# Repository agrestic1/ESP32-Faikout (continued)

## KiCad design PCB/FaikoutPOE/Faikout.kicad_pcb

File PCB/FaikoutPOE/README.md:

# FaikoutPOE

## Trademark

This project is subject to the licence in the LICENCE file, and even if that says it is an open source project, you cannot sell boards or cases bearing the Andrews & Arnold Ltd name, the A&A logo, the registered trademark AJK logo, or other registered trademarks, or any GS1 allocated EANs/barcode assigned to Andrews & Arnold Ltd.

## PCB Designs

These files are for use with [KiCAD](https://www.kicad.org).

- [Faikout](Faikout.kicad_pro)

## 3D

3D case designs are normally automatically created from the PCB so as to ensure correct details and placement of apertures, etc.

|Design|Bottom|Top|Combined|
|------|------|---|--------|
|Faikout||||

## PCB Images Faikout

---

*Auto generated README.md 2026-10-20T12:44:44*

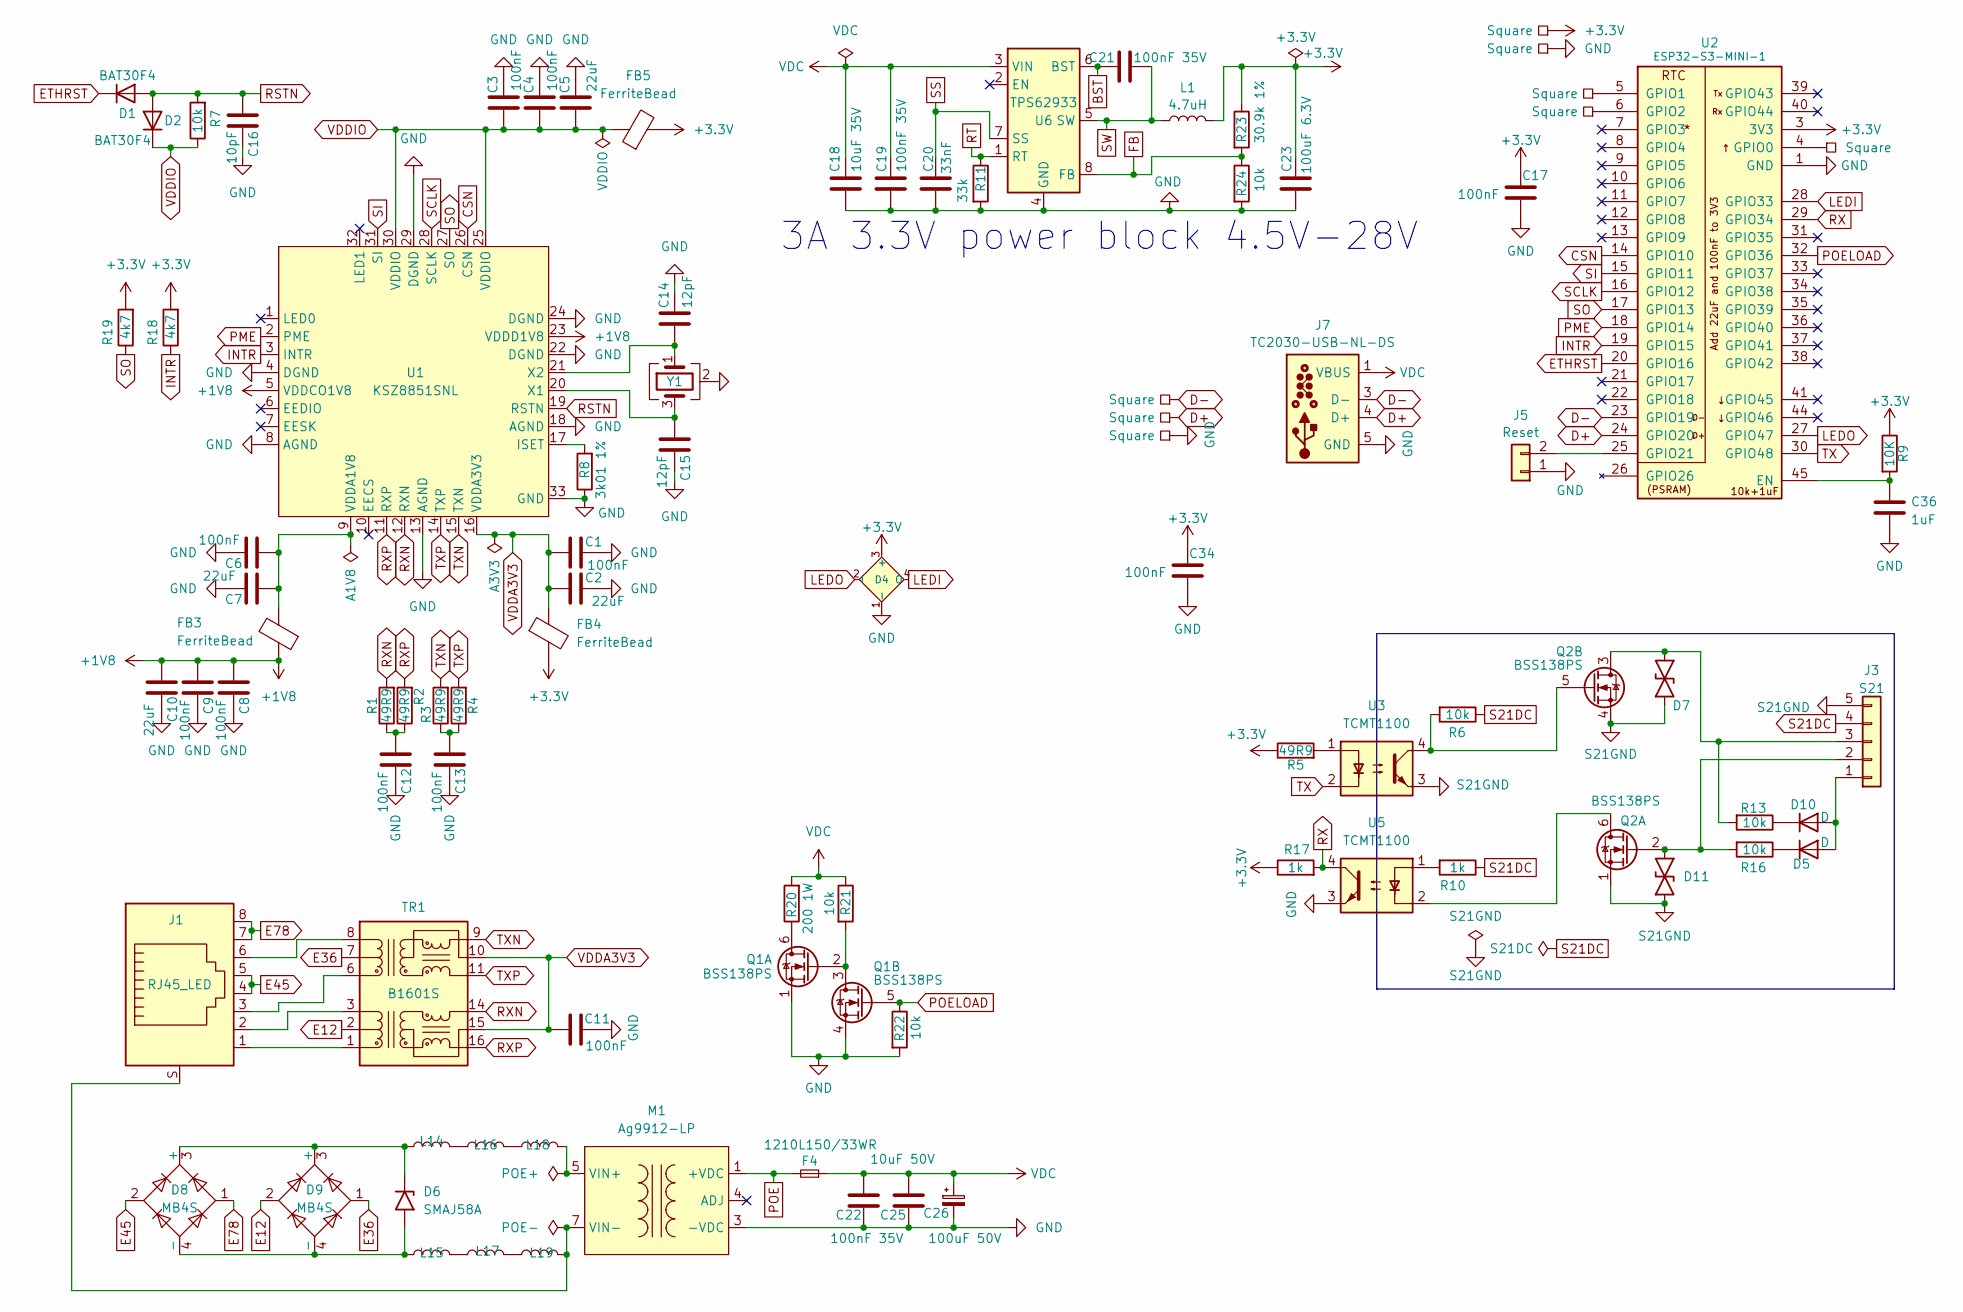
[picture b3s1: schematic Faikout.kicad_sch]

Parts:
C1, C3, C4, C6, C8, C9, C11, C12, C13: 100nF; C_0201; MPN C66938
C2, C5, C7, C10: 22uF; C_0402; MPN C105226
C14, C15: 12pF; C_0201
C16: 10pF; C_0201; MPN C76921
C17, C34: 100nF; C_0201; MPN C76934
C18: 10uF 35V; C_0603; MPN C22367827
C19, C21, C22: 100nF 35V; C_0201; MPN C181043
C20: 33nF; C_0201; MPN C5142554
C23: 100uF 6.3V; C_0805; MPN C141660
C25: 10uF 50V; C_1206; MPN C13585
C26: 100uF 50V; CP_Elec_6.3x7.7; MPN C72478
C36: 1uF; C_0201
D1, D2: BAT30F4; D_0201; MPN C18197832
D4: XL-1615RGBC-2812B; SMD1615-Side; MPN C5349954
D5, D10: D; D_0402; MPN C28642302
D6: SMAJ58A; D_SMA
D7, D11: DFN1006-2L; MPN C5137770
D8, D9: MB4S; TO-269AA-BR; MPN C232847
F4: 1210L150/33WR; Fuse_1210; MPN C42376299
FB3, FB4, FB5: FerriteBead; L_0603; MPN C14709
J1: RJ45_LED; RC01516; MPN C708636
J3: S21; JST_EH_S5B-EH_1x05_P2.50mm_Horizontal; MPN C265103
J5: Reset; AA-Pad
J7: TC2030-USB-NL-DS; Tag-Connect_TC2030-IDC-NL_2x03_P1.27mm_Vertical
L1: 4.7uH; L_6x6; MPN C32684
L14, L15, L16, L17, L18, L19: CBG201209U121T; L_0805; MPN C41330
M1: Ag9912-LP; Ag9900-LP; MPN C6789853
P1, P2, P3, P4, P5, P6, P7, P8: Square; PAD-2mm
Q1, Q2: BSS138PS; SOT-363_SC-70-6; MPN C193381
R1, R2, R3, R4, R5: 49R9; R_0201; MPN C100141
R6, R7, R13, R16, R21, R22, R24: 10k; R_0201; MPN C106225
R8: 3k01 1%; R_0201; MPN C320817
R9: 10K; R_0201; MPN C106225
R10, R17: 1k; R_0201; MPN C270365
R11: 33k; R_0201; MPN C473534
R18, R19: 4k7; R_0201; MPN C138135
R20: 200 1W; R_2512; MPN C2907575
R23: 30.9k 1%; R_0201; MPN C473585
TR1: B1601S; MPN C510548
U1: KSZ8851SNL; QFN-32-1EP_5x5mm_P0.5mm_EP3.7x3.7mm-hot; MPN C633272
U2: ESP32-S3-MINI-1; MPN C3013941
U3: TCMT1100; SOP-4_4.4x2.6mm_P1.27mm; MPN C118298
U5: TCMT1100; SOP-4_4.4x2.6mm_P1.27mm; MPN MPN
U6: TPS62933; SOT-583-8; MPN C3200405
Y1: Crystal_GND24; Crystal-3.2x2.5; MPN C5155480

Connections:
+1V8: C8.1, C9.1, C10.1, FB3.1, U1.5 (VDDCO1V8), U1.23 (VDDD1V8)
+3.3V: C17.2, C23.1, C34.2, D4.3 (+), FB4.2, FB5.2, L1.2, P7.1 (P_1), R5.1, R9.1, R17.1, R18.2, R19.2, R23.1, U2.3 (3V3)
BST: C21.1, U6.6 (BST)
CSN: U1.26 (CSN), U2.14 (GPIO10)
D+: J7.4 (D+), P3.1 (P_1), U2.24 (GPIO20)
D-: J7.2 (NC), J7.3 (D-), J7.6 (NC), P2.1 (P_1), U2.23 (GPIO19)
E12: D9.2, TR1.2 (C_TD)
E36: D9.1, TR1.7 (C_RD)
E45: D8.2, J1.4, J1.5
E78: D8.1, J1.7, J1.8
ETHRST: D1.1 (K), U2.20 (GPIO16)
FB: R23.2, R24.1, U6.8 (FB)
GND: C1.2, C2.2, C3.2, C4.2, C5.2, C6.2, C7.2, C8.2, C9.2, C10.2, C11.2, C12.2, C13.2, C14.2, C15.2, C16.2, C17.1, C18.2, C19.2, C20.2, C22.2, C23.2, C25.1, C26.2, C34.1, C36.2, D4.1 (-), J5.1, J7.5 (GND), M1.3 (-VDC), P4.1 (P_1), P8.1 (P_1), Q1.1 (SN), Q1.4 (DP), R8.1, R11.2, R22.2, R24.2, U1.4 (DGND), U1.8 (AGND), U1.13 (AGND), U1.18 (AGND), U1.22 (DGND), U1.24 (DGND), U1.29 (DGND), U1.33 (GND), U2.1 (GND), U2.2 (GND), U2.42 (GND), U2.43 (GND), U2.46 (GND), U2.47 (GND), U2.48 (GND), U2.49 (GND), U2.50 (GND), U2.51 (GND), U2.52 (GND), U2.53 (GND), U2.54 (GND), U2.55 (GND), U2.56 (GND), U2.57 (GND), U2.58 (GND), U2.59 (GND), U2.60 (GND), U2.61 (GND), U2.62 (GND), U2.63 (GND), U2.64 (GND), U2.65 (GND), U5.3, U6.4 (GND), Y1.2 (G), Y1.4 (G)
INTR: R18.1, U1.3 (INTR), U2.19 (GPIO15)
LEDI: D4.4 (O), U2.28 (GPIO33)
LEDO: D4.2 (I), U2.27 (GPIO47)
unnamed: C12.1, R1.1, R2.1
unnamed: C13.1, R3.1, R4.1
unnamed: D5.1 (K), R16.1
unnamed: D6.1 (A1), D8.3 (+), D9.3 (+), L14.1
unnamed: D6.2 (A2), D8.4 (-), D9.4 (-), L15.1
unnamed: D5.2 (A), D10.2 (A), J3.1
unnamed: D10.1 (K), R13.1
unnamed: D11.1, J3.2, Q2.2 (GN), R16.2
unnamed: D7.2, J3.3, Q2.3 (SP), R13.2
unnamed: J5.2, U2.25 (GPIO21)
unnamed: L14.2, L16.1
unnamed: L15.2, L17.1
unnamed: L16.2, L18.1
unnamed: L17.2, L19.1
unnamed: P1.1 (P_1), U2.4 (GPIO0)
unnamed: P5.1 (P_1), U2.5 (GPIO1)
unnamed: P6.1 (P_1), U2.6 (GPIO2)
unnamed: Q1.6 (DN), R20.1
unnamed: Q1.2 (GN), Q1.3 (SP), R21.2
unnamed: Q2.6 (DN), U5.2
unnamed: Q2.5 (GP), R6.2, U3.4
unnamed: R5.2, U3.1
unnamed: R10.2, U5.1
unnamed: J1.3, TR1.6 (RD+)
unnamed: J1.6, TR1.8 (RD-)
unnamed: J1.1, TR1.1 (TD+)
unnamed: J1.2, TR1.3 (TD-)
unnamed: R8.2, U1.17 (ISET)
unnamed: C6.1, C7.1, FB3.2, U1.9 (VDDA1V8)
unnamed: C15.1, U1.20 (X1), Y1.3
unnamed: C14.1, U1.21 (X2), Y1.1
unnamed: C36.1, R9.2, U2.45 (EN)
PME: U1.2 (PME), U2.18 (GPIO14)
POE: F4.2, M1.1 (+VDC), M1.2 (+VDC)
POELOAD: Q1.5 (GP), R22.1, U2.32 (GPIO36)
RSTN: C16.1, D1.2 (A), D2.2 (A), R7.2, U1.19 (RSTN)
RT: R11.1, U6.1 (RT)
RX: R17.2, U2.29 (GPIO34), U5.4
RXN: R1.2, TR1.14 (TX-), U1.12 (RXN)
RXP: R2.2, TR1.16 (TX+), U1.11 (RXP)
S21DC: J3.4, R6.1, R10.1
S21GND: D7.1, D11.2, J3.5, Q2.1 (SN), Q2.4 (DP), U3.3
SCLK: U1.28 (SCLK), U2.16 (GPIO12)
SI: U1.31 (SI), U2.15 (GPIO11)
SO: R19.1, U1.27 (SO), U2.17 (GPIO13)
SS: C20.1, U6.7 (SS)
SW: C21.2, L1.1, U6.5 (SW)
TX: U2.30 (GPIO48), U3.2
TXN: R3.2, TR1.9 (RX-), U1.15 (TXN)
TXP: R4.2, TR1.11 (RX+), U1.14 (TXP)
VDC: C18.1, C19.1, C22.1, C25.2, C26.1, F4.1, J7.1 (VBUS), R20.2, R21.1, U6.3 (VIN)
VDDA3V3: C1.1, C2.1, C11.1, FB4.1, TR1.10 (C_RX), TR1.15 (C_TX), U1.16 (VDDA3V3)
VDDIO: C3.1, C4.1, C5.1, D2.1 (K), FB5.1, R7.1, U1.25 (VDDIO), U1.30 (VDDIO)
VIN+: L18.2, M1.5 (VIN+), M1.6 (VIN+)
VIN-: J1.S, L19.2, M1.7 (VIN-), M1.8 (VIN-)

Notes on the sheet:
3A 3.3V power block 4.5V-28V

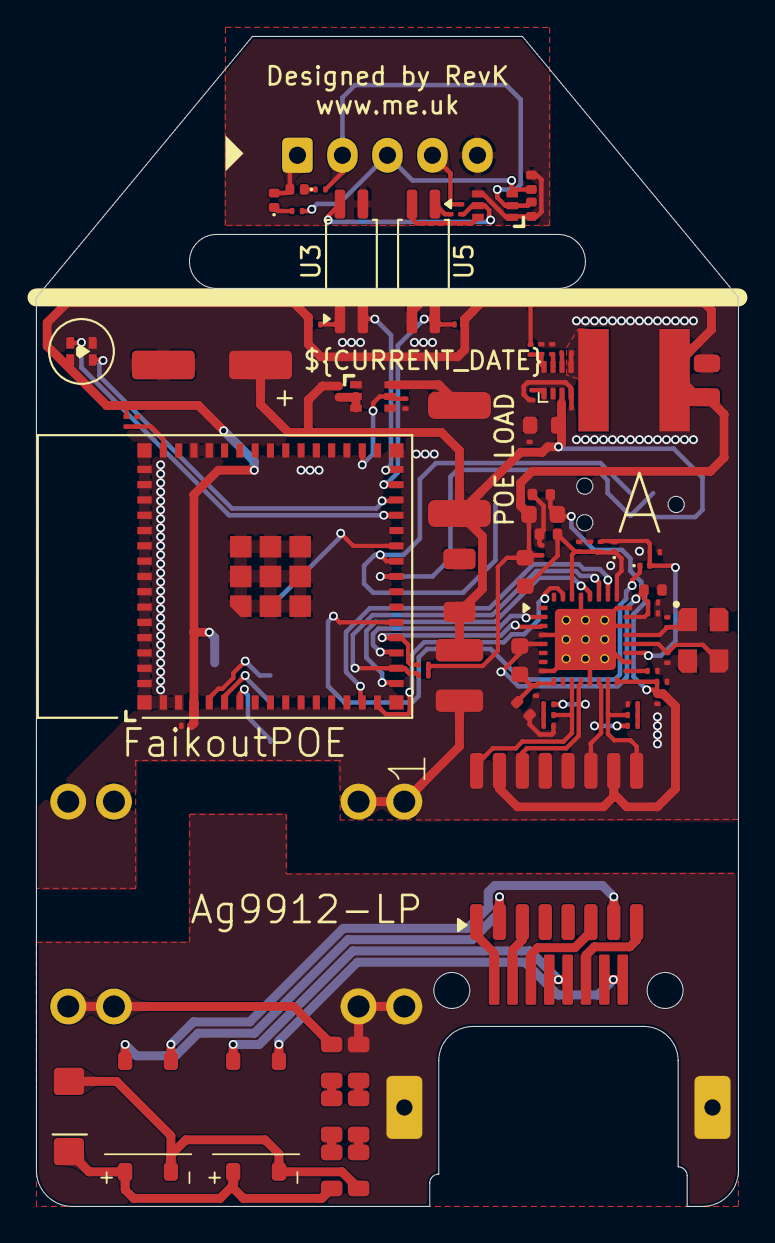
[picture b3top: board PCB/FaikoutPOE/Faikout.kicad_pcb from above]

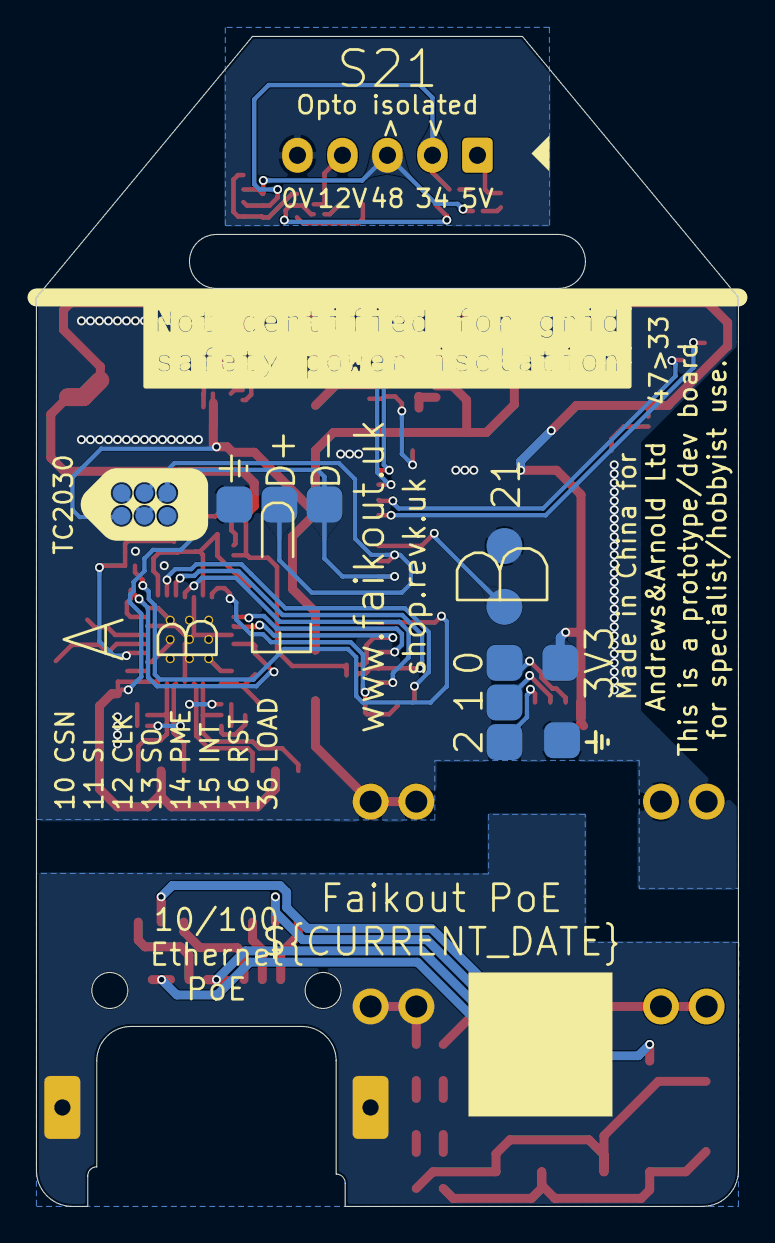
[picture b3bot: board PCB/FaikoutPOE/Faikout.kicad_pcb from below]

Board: 2 copper layers, 39.0 x 65.0 mm, 91 parts (10 on the bottom side), 71 nets.
